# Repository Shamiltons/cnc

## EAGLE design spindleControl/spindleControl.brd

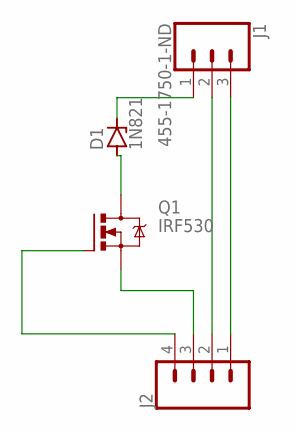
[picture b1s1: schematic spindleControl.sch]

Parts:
D1: 1N821; DO35Z10
J1: 455-1750-1-ND; 1X03
J2: CONN_04PTH; 1X04
Q1: IRF530; TO220BV

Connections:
unnamed: J2.4, Q1.G
unnamed: J2.3, Q1.S
unnamed: D1.A, Q1.D
unnamed: D1.C, J1.1
unnamed: J1.2, J2.2
unnamed: J1.3, J2.1

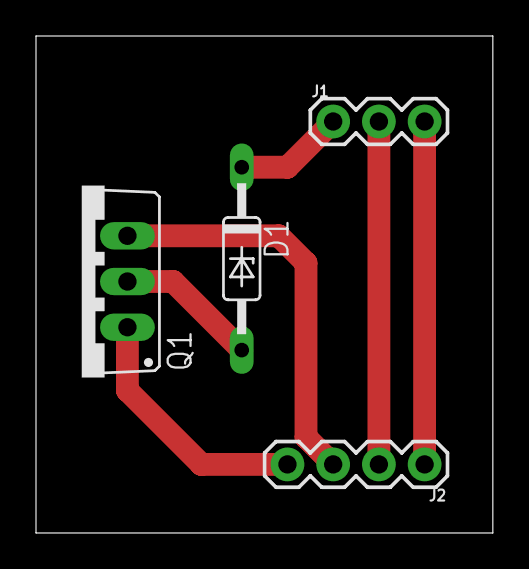
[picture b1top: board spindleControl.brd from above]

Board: 2 copper layers, 25.4 x 27.6 mm, 4 parts (0 on the bottom side), 6 nets.

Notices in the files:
parts and their libraries:
SparkFun-Connectors: Licensing: Creative Commons ShareAlike 4.0 International - https://creativecommons.org/licenses/by-sa/4.0
